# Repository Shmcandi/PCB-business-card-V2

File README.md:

# ESP32-C6 Smart PCB Business Card V2 (96-RGB Matrix + Dual NFC/RFID)

An ultra-slim, monolithic smart electronic business card in the standard ISO/IEC 7810 ID-1 credit card form factor ($85.6 \times 54.0\text{ mm}$), powered by an **Espressif ESP32-C6-MINI-1** microcontroller.

Featuring an ultra-dense **96-LED addressable RGB micro-matrix (WS2812B-2020)** on the front, and a **Dual-Frequency 13.56 MHz NFC + 125 kHz RFID Contactless Engine** on the back with an integrated 4-turn planar spiral antenna etched directly in PCB copper.

Tap against any modern smartphone (iPhone / Android) to instantly deliver your digital portfolio and vCard, or tap against office turnstiles and RFID access readers to unlock doors — with onboard USB-C programming, autonomous Li-Po battery charging, and zero-drain hardware deep sleep.

Everything is engineered for 100% surface-mount assembly with **zero pin headers, zero through-holes, and zero sockets**.

---

## 📸 3D Renders

| Isometric Perspective View | Top View (96-LED Field) | Bottom View (Antenna & Battery Bay) |
| :---: | :---: | :---: |
|  |  |  |

---

## ⚡ Key Specifications & Features

- **Form Factor:** $85.6\text{ mm} \times 54.0\text{ mm} \times 1.6\text{ mm}$ (Standard ID-1 Credit Card Size with $3.18\text{ mm}$ corner radii). Fits standard wallets and card holders.
- **Microcontroller:** **ESP32-C6-MINI-1-N4**
  - High-performance 32-bit RISC-V core (up to 160 MHz) + ultra-low-power RISC-V coprocessor (up to 20 MHz)
  - 2.4 GHz Wi-Fi 6 (802.11ax), Bluetooth 5 (LE), Zigbee 3.0 & Thread (802.15.4 / Matter)
  - Onboard PCB trace antenna with dedicated RF copper clearance keepout
- **Display Matrix:** **96 Addressable RGB Micro-LEDs (WS2812B-2020)**
  - Arranged in a $12 \times 8$ grid ($4.0\text{ mm} \times 4.0\text{ mm}$ pitch) spanning $48.0\text{ mm} \times 32.0\text{ mm}$ across the front
  - Compact $2.0\text{ mm} \times 2.0\text{ mm}$ package with integrated constant-current driver ICs
  - Full 24-bit true color (16.7 million colors) per pixel, driven over a single high-speed GPIO line (`GPIO14`)
  - Serpentine daisy-chain layout with optimized collinear traces for maximum signal integrity
- **Dual-Frequency Contactless Subsystem (NFC + RFID):**
  1. **13.56 MHz High-Frequency NFC (ISO 14443A / NFC Forum Type 2):**
     - Powered by **NXP NTAG I2C Plus (`NT3H2111W0FHK`)** in a TSSOP-8 package
     - Connected to a **4-turn rectangular planar spiral loop antenna** etched directly into the bottom copper layer (`B_Cu`)
     - Resonates at $13.56\text{ MHz}$ with NTAG's $50\text{ pF}$ internal tuning capacitance
     - **Dual Interface:** Operates 100% passively without battery from the smartphone's RF field, and updates dynamically over I2C (`GPIO6` / `GPIO7`) from the ESP32-C6
     - **Field Detect Interrupt (`GPIO18`):** Wakes the ESP32 from deep sleep or triggers LED celebration animations when a smartphone is tapped
  2. **125 kHz Low-Frequency RFID (Building & Door Access):**
     - Powered by **Atmel/Microchip T5577 (`ATA5577C`)** transponder IC in SOIC-8
     - Emulates 125 kHz proximity cards (EM4100 / EM4200 40-bit IDs, HID ProxCard II, Indala) for office doors and turnstiles
     - Dual antenna interface: SMD 1812 transponder inductor (`L1`) + dedicated solder pads (`J3`) for thin wound enamel wire coils
     - **Active Modulation:** Features an onboard **BSS138 N-channel MOSFET (`Q2`)** driven by `GPIO1` (`RFID_MOD`) enabling active software-defined Manchester load modulation
- **Hardware Deep-Sleep Power Gate (Zero Standby Drain):**
  - Standard WS2812B LEDs consume $\sim 1\text{ mA}$ of static quiescent current per pixel even when turned black ($96\text{ LEDs} \approx 96\text{ mA}$ quiescent draw)
  - Incorporates an onboard **Diodes Inc DMG2305UX P-Channel MOSFET** load switch driven by `GPIO5` (`LED_EN`)
  - Physically disconnects the $V_{LED}$ power rail during ESP32 deep sleep, reducing standby current to microamps and enabling months of battery life
- **USB-C Interface:**
  - GCT USB4105 16-pin USB Type-C receptacle with $5.1\text{ k}\Omega$ CC pull-down resistors (compliant with USB-C PD / fast chargers)
  - Native USB-Serial/JTAG directly connected to ESP32-C6 `GPIO12` (D-) and `GPIO13` (D+) for instant flashing and serial logging without external UART bridges
- **Power & Li-Po Battery Charging:**
  - Autonomous Li-Po charger: Microchip **MCP73831T-2ACI/OT** ($300\text{ mA}$ charge rate) with red charging status LED (`CHG`)
  - High-efficiency LDO regulator: Diodes Inc **AP2112K-3.3** ($600\text{ mA}$ peak current, $55\,\mu\text{A}$ quiescent current, low dropout voltage)
  - Battery connector: SMD horizontal JST-PH 2-pin connector (`J2`) + dedicated rear $30 \times 25\text{ mm}$ silkscreen area for mounting an ultra-slim $3.7\text{V}$ Li-Po pouch cell (`302030` / `402030`, $150\text{–}250\text{ mAh}$)
- **Interactive Tactile Controls:**
  - `EN` (Reset) tactile switch (`SW1`) with RC debounce filter
  - `BOOT` (`GPIO9`) tactile switch (`SW2`) for firmware download / user interaction
  - `USER` (`GPIO4`) tactile switch (`SW3`) for mode cycling / games / menu navigation

---

## 📌 ESP32-C6 Pinout & Signal Mapping

| Signal | ESP32-C6 Pin | GPIO / Function | Electrical Type | Description |
| :--- | :---: | :---: | :---: | :--- |
| **LED_DIN** | Pin 19 | GPIO14 | Digital Output | Matrix Serial Data Input (800 kHz NZR stream) |
| **LED_EN** | Pin 10 | GPIO5 | Digital Output | LED Power Gate (Active-LOW: `LOW` = ON, `HIGH` = OFF) |
| **I2C_SDA** | Pin 12 | GPIO6 | I2C Open-Drain | NTAG I2C Plus Serial Data Line (4.7k pull-up to 3.3V) |
| **I2C_SCL** | Pin 13 | GPIO7 | I2C Open-Drain | NTAG I2C Plus Serial Clock Line (4.7k pull-up to 3.3V) |
| **NFC_FD** | Pin 24 | GPIO18 | Digital Input | NTAG Field Detect Interrupt (Active-LOW with 10k pull-up) |
| **RFID_MOD**| Pin 6 | GPIO1 | Digital Output | 125 kHz Active Load Modulation Gate via Q2 BSS138 |
| **USER_SW** | Pin 9 | GPIO4 | Digital Input | Tactile Pushbutton (Active-LOW with internal pull-up) |
| **BOOT_SW** | Pin 23 | GPIO9 | Digital Input | Boot Mode / User Button 2 (Active-LOW) |
| **RESET_SW**| Pin 8 | CHIP_EN | Reset / Enable | Active-LOW Hardware Reset with 10k pull-up + 100nF filter |
| **USB D-** | Pin 17 | GPIO12 | Differential D- | Native ESP32 USB-Serial/JTAG Data Minus |
| **USB D+** | Pin 18 | GPIO13 | Differential D+ | Native ESP32 USB-Serial/JTAG Data Plus |
| **CHG_STAT**| — | — | Open-Drain | MCP73831 Charge Indicator to Red LED `D1` |

---

## 🧮 Matrix Geometry & Serpentine Mapping

The 96 LEDs are placed in an alternating serpentine pattern to minimize trace length and eliminate cross-routing:

```
Row 0 (y=0):  LED  0  <--  LED  1  <-- ... <--  LED 11  (Right-to-Left, 0° rotation)
               |
Row 1 (y=1):  LED 12  -->  LED 13  --> ... -->  LED 23  (Left-to-Right, 180° rotation)
                                                 |
Row 2 (y=2):  LED 24  <--  LED 25  <-- ... <--  LED 35  (Right-to-Left, 0° rotation)
               |
Row 3 (y=3):  ... (repeats for 8 rows, ending at LED 95)
```

### Coordinate Conversion Function (FastLED / NeoPixel)

```cpp
// Map (x, y) coordinates where x is [0..11] and y is [0..7]
uint16_t XY(uint8_t x, uint8_t y) {
    if (x >= 12 || y >= 8) return 0;
    if (y & 0x01) {
        // Odd rows: Left to Right
        return (y * 12) + x;
    } else {
        // Even rows: Right to Left
        return (y * 12) + (11 - x);
    }
}
```

---

## 📦 Hardware & Manufacturing Files

The board is 100% routed and verified with KiCad 10 DRC (0 unconnected items, 0 clearance errors), ready for turnkey assembly at JLCPCB / PCBWay:

- **KiCad PCB:** [`card_v2.kicad_pcb`](card_v2.kicad_pcb)
- **KiCad Project:** [`card_v2.kicad_pro`](card_v2.kicad_pro)
- **Order-Ready Gerbers Archive:** [`pcb_business_card_v2_gerbers.zip`](pcb_business_card_v2_gerbers.zip)
- **Bill of Materials (BOM):** [`fab_v2/BOM.csv`](fab_v2/BOM.csv)
- **Pick-and-Place Centroids (CPL):** [`fab_v2/CPL.csv`](fab_v2/CPL.csv)
- **Custom Footprints:** [`custom.pretty/`](custom.pretty/)

### Recommended Fabrication Settings:
| Parameter | Recommended Value |
| :--- | :--- |
| **Layers** | 2 Layers |
| **PCB Thickness** | 1.6 mm (standard) or 1.0 mm (ultra-slim wallet profile) |
| **Solder Mask** | Matte Black (best contrast for RGB LEDs) |
| **Silkscreen** | White |
| **Surface Finish** | ENIG (Electroless Nickel Immersion Gold) |
| **Copper Weight** | 1 oz Cu |

---

## 📜 License & Author

Designed and engineered by **Shmcandi**. Released under the **MIT License**.

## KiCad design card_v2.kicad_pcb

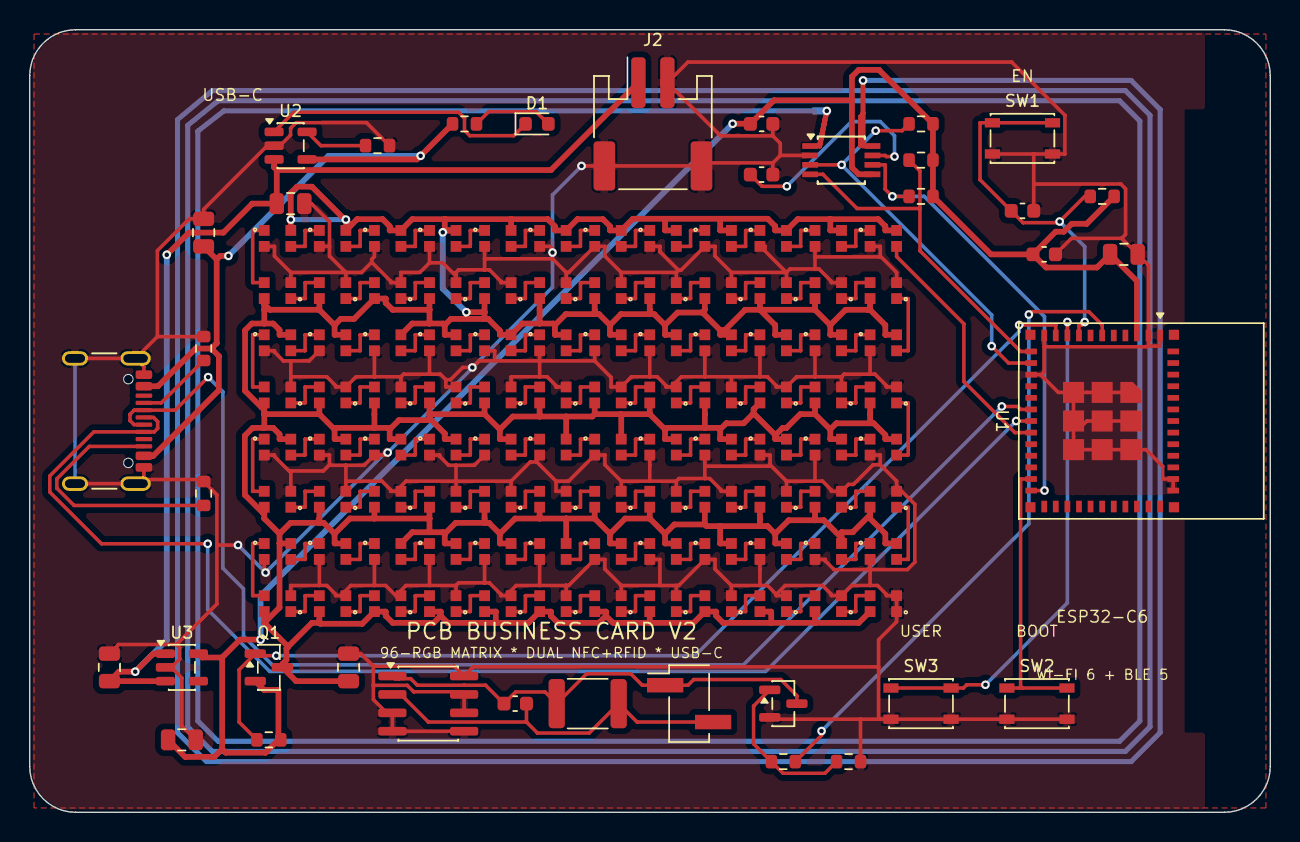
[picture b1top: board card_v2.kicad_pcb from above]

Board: 2 copper layers, 85.6 x 54.0 mm, 134 parts (1 on the bottom side), 122 nets.

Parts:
C1, C2: 4.7uF; C_0805_2012Metric
C3, C4, C6, C8: 10uF; C_0805_2012Metric
C5, C9, C10: 100nF; C_0603_1608Metric
C7: 1uF; C_0603_1608Metric
C12: 470pF; C_0603_1608Metric
D1: CHG; LED_0603_1608Metric
J1: USB-C (USB4105); USB_C_Receptacle_GCT_USB4105-xx-A_16P_TopMnt_Horizontal
J2: BATT JST-PH; JST_PH_S2B-PH-SM4-TB_1x02-1MP_P2.00mm_Horizontal
J3: 125k Wire Pads; PinHeader_1x02_P2.54mm_Vertical_SMD_Pin1Left
L1: 125kHz Coil; L_1812_4532Metric
LED1, LED2, LED3, LED4, LED5, LED6, LED7, LED8, LED9, LED10, LED11, LED12, LED13, LED14, LED15, LED16, LED17, LED18, LED19, LED20, LED21, LED22, LED23, LED24, LED25, LED26, LED27, LED28, LED29, LED30, LED31, LED32, LED33, LED34, LED35, LED36, LED37, LED38, LED39, LED40, LED41, LED42, LED43, LED44, LED45, LED46, LED47, LED48, LED49, LED50, LED51, LED52, LED53, LED54, LED55, LED56, LED57, LED58, LED59, LED60, LED61, LED62, LED63, LED64, LED65, LED66, LED67, LED68, LED69, LED70, LED71, LED72, LED73, LED74, LED75, LED76, LED77, LED78, LED79, LED80, LED81, LED82, LED83, LED84, LED85, LED86, LED87, LED88, LED89, LED90, LED91, LED92, LED93, LED94, LED95, LED96: WS2812B-2020; LED_WS2812B-2020
NT1: NetTie-2; NetTie-2_SMD_Pad0.5mm
Q1: DMG2305UX; SOT-23
Q2: BSS138; SOT-23
R1, R2: 5.1k; R_0603_1608Metric
R3: 3.3k; R_0603_1608Metric
R4, R10: 10k; R_0603_1608Metric
R6, R11: 1k; R_0603_1608Metric
R7, R12: 100k; R_0603_1608Metric
R8, R9: 4.7k; R_0603_1608Metric
SW1: EN; SW_SPST_PTS810
SW2: BOOT; SW_SPST_PTS810
SW3: USER; SW_SPST_PTS810
U1: ESP32-C6-MINI-1-N4; ESP32-C6-MINI-1
U2: MCP73831T-2ACI/OT; SOT-23-5
U3: AP2112K-3.3; SOT-23-5
U4: NT3H2111W0FHK; TSSOP-8_3x3mm_P0.65mm
U5: ATA5577C; SOIC-8_3.9x4.9mm_P1.27mm

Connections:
3V3: C4.1, C5.1, C6.1, C9.1, Q1.2, R4.2, R7.2, R8.2, R9.2, R10.2, U1.3, U3.5, U4.5
BOOT: SW2.1, U1.23
BTN: SW3.1, U1.9
CC1: J1.A5, R1.1
CC2: J1.B5, R2.1
D_SIG_0: LED1.3, U1.19
D_SIG_1: LED1.1, LED2.3
D_SIG_2: LED2.1, LED3.3
D_SIG_3: LED3.1, LED4.3
D_SIG_4: LED4.1, LED5.3
D_SIG_5: LED5.1, LED6.3
D_SIG_6: LED6.1, LED7.3
D_SIG_7: LED7.1, LED8.3
D_SIG_8: LED8.1, LED9.3
D_SIG_9: LED9.1, LED10.3
D_SIG_10: LED10.1, LED11.3
D_SIG_11: LED11.1, LED12.3
D_SIG_12: LED12.1, LED13.3
D_SIG_13: LED13.1, LED14.3
D_SIG_14: LED14.1, LED15.3
D_SIG_15: LED15.1, LED16.3
D_SIG_16: LED16.1, LED17.3
D_SIG_17: LED17.1, LED18.3
D_SIG_18: LED18.1, LED19.3
D_SIG_19: LED19.1, LED20.3
D_SIG_20: LED20.1, LED21.3
D_SIG_21: LED21.1, LED22.3
D_SIG_22: LED22.1, LED23.3
D_SIG_23: LED23.1, LED24.3
D_SIG_24: LED24.1, LED25.3
D_SIG_25: LED25.1, LED26.3
D_SIG_26: LED26.1, LED27.3
D_SIG_27: LED27.1, LED28.3
D_SIG_28: LED28.1, LED29.3
D_SIG_29: LED29.1, LED30.3
D_SIG_30: LED30.1, LED31.3
D_SIG_31: LED31.1, LED32.3
D_SIG_32: LED32.1, LED33.3
D_SIG_33: LED33.1, LED34.3
D_SIG_34: LED34.1, LED35.3
D_SIG_35: LED35.1, LED36.3
D_SIG_36: LED36.1, LED37.3
D_SIG_37: LED37.1, LED38.3
D_SIG_38: LED38.1, LED39.3
D_SIG_39: LED39.1, LED40.3
D_SIG_40: LED40.1, LED41.3
D_SIG_41: LED41.1, LED42.3
D_SIG_42: LED42.1, LED43.3
D_SIG_43: LED43.1, LED44.3
D_SIG_44: LED44.1, LED45.3
D_SIG_45: LED45.1, LED46.3
D_SIG_46: LED46.1, LED47.3
D_SIG_47: LED47.1, LED48.3
D_SIG_48: LED48.1, LED49.3
D_SIG_49: LED49.1, LED50.3
D_SIG_50: LED50.1, LED51.3
D_SIG_51: LED51.1, LED52.3
D_SIG_52: LED52.1, LED53.3
D_SIG_53: LED53.1, LED54.3
D_SIG_54: LED54.1, LED55.3
D_SIG_55: LED55.1, LED56.3
D_SIG_56: LED56.1, LED57.3
D_SIG_57: LED57.1, LED58.3
D_SIG_58: LED58.1, LED59.3
D_SIG_59: LED59.1, LED60.3
D_SIG_60: LED60.1, LED61.3
D_SIG_61: LED61.1, LED62.3
D_SIG_62: LED62.1, LED63.3
D_SIG_63: LED63.1, LED64.3
D_SIG_64: LED64.1, LED65.3
D_SIG_65: LED65.1, LED66.3
D_SIG_66: LED66.1, LED67.3
D_SIG_67: LED67.1, LED68.3
D_SIG_68: LED68.1, LED69.3
D_SIG_69: LED69.1, LED70.3
D_SIG_70: LED70.1, LED71.3
D_SIG_71: LED71.1, LED72.3
D_SIG_72: LED72.1, LED73.3
D_SIG_73: LED73.1, LED74.3
D_SIG_74: LED74.1, LED75.3
D_SIG_75: LED75.1, LED76.3
D_SIG_76: LED76.1, LED77.3
D_SIG_77: LED77.1, LED78.3
D_SIG_78: LED78.1, LED79.3
D_SIG_79: LED79.1, LED80.3
D_SIG_80: LED80.1, LED81.3
D_SIG_81: LED81.1, LED82.3
D_SIG_82: LED82.1, LED83.3
D_SIG_83: LED83.1, LED84.3
D_SIG_84: LED84.1, LED85.3
D_SIG_85: LED85.1, LED86.3
D_SIG_86: LED86.1, LED87.3
D_SIG_87: LED87.1, LED88.3
D_SIG_88: LED88.1, LED89.3
D_SIG_89: LED89.1, LED90.3
D_SIG_90: LED90.1, LED91.3
D_SIG_91: LED91.1, LED92.3
D_SIG_92: LED92.1, LED93.3
D_SIG_93: LED93.1, LED94.3
D_SIG_94: LED94.1, LED95.3
D_SIG_95: LED95.1, LED96.3
EN: C7.1, R4.1, SW1.1, U1.8
GND: C1.2, C2.2, C3.2, C4.2, C5.2, C6.2, C7.2, C8.2, C9.2, C10.2, J1.A1, J1.A12, J1.B1, J1.B12, J1.SH, J2.2, J2.MP, LED1.2, LED2.2, LED3.2, LED4.2, LED5.2, LED6.2, LED7.2, LED8.2, LED9.2, LED10.2, LED11.2, LED12.2, LED13.2, LED14.2, LED15.2, LED16.2, LED17.2, LED18.2, LED19.2, LED20.2, LED21.2, LED22.2, LED23.2, LED24.2, LED25.2, LED26.2, LED27.2, LED28.2, LED29.2, LED30.2, LED31.2, LED32.2, LED33.2, LED34.2, LED35.2, LED36.2, LED37.2, LED38.2, LED39.2, LED40.2, LED41.2, LED42.2, LED43.2, LED44.2, LED45.2, LED46.2, LED47.2, LED48.2, LED49.2, LED50.2, LED51.2, LED52.2, LED53.2, LED54.2, LED55.2, LED56.2, LED57.2, LED58.2, LED59.2, LED60.2, LED61.2, LED62.2, LED63.2, LED64.2, LED65.2, LED66.2, LED67.2, LED68.2, LED69.2, LED70.2, LED71.2, LED72.2, LED73.2, LED74.2, LED75.2, LED76.2, LED77.2, LED78.2, LED79.2, LED80.2, LED81.2, LED82.2, LED83.2, LED84.2, LED85.2, LED86.2, LED87.2, LED88.2, LED89.2, LED90.2, LED91.2, LED92.2, LED93.2, LED94.2, LED95.2, LED96.1, LED96.2, Q2.2, R1.2, R2.2, R3.2, R12.2, SW1.2, SW2.2, SW3.2, U1.1, U1.2, U1.11, U1.14, U1.36, U1.37, U1.49, U2.2, U3.2, U4.2, U5.3, U5.4, U5.5, U5.6, U5.7, U5.8
I2C_SCL: R8.1, U1.13, U4.3
I2C_SDA: R9.1, U1.12, U4.4
LEDA: D1.2, R6.2
LED_EN: Q1.1, R7.1, U1.10
NFC_ANT_A: NT1.1, U4.1
NFC_ANT_B: NT1.2, U4.8
NFC_FD: R10.1, U1.24, U4.6
PROG: R3.1, U2.5
RFID_COIL1: C12.1, J3.1, L1.1, Q2.3, U5.1
RFID_COIL2: C12.2, J3.2, L1.2, U5.2
RFID_GATE: Q2.1, R11.1, R12.1
RFID_MOD: R11.2, U1.6
STAT: D1.1, U2.1
USB_DN: J1.A7, J1.B7, U1.17
USB_DP: J1.A6, J1.B6, U1.18
VBAT: C2.1, C3.1, J2.1, U2.3, U3.1, U3.3
VBUS: C1.1, J1.A4, J1.A9, J1.B4, J1.B9, R6.1, U2.4
VLED: C8.1, LED1.4, LED2.4, LED3.4, LED4.4, LED5.4, LED6.4, LED7.4, LED8.4, LED9.4, LED10.4, LED11.4, LED12.4, LED13.4, LED14.4, LED15.4, LED16.4, LED17.4, LED18.4, LED19.4, LED20.4, LED21.4, LED22.4, LED23.4, LED24.4, LED25.4, LED26.4, LED27.4, LED28.4, LED29.4, LED30.4, LED31.4, LED32.4, LED33.4, LED34.4, LED35.4, LED36.4, LED37.4, LED38.4, LED39.4, LED40.4, LED41.4, LED42.4, LED43.4, LED44.4, LED45.4, LED46.4, LED47.4, LED48.4, LED49.4, LED50.4, LED51.4, LED52.4, LED53.4, LED54.4, LED55.4, LED56.4, LED57.4, LED58.4, LED59.4, LED60.4, LED61.4, LED62.4, LED63.4, LED64.4, LED65.4, LED66.4, LED67.4, LED68.4, LED69.4, LED70.4, LED71.4, LED72.4, LED73.4, LED74.4, LED75.4, LED76.4, LED77.4, LED78.4, LED79.4, LED80.4, LED81.4, LED82.4, LED83.4, LED84.4, LED85.4, LED86.4, LED87.4, LED88.4, LED89.4, LED90.4, LED91.4, LED92.4, LED93.4, LED94.4, LED95.4, LED96.4, Q1.3
VOUT_NFC: C10.1, U4.7

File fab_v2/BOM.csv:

Comment/Value,Designator,Footprint,Quantity
100k,"R7, R12",R_0603_1608Metric,2
100nF,"C5, C9, C10",C_0603_1608Metric,3
10k,"R4, R10",R_0603_1608Metric,2
10uF,"C3, C4, C6, C8",C_0805_2012Metric,4
125k Wire Pads,J3,PinHeader_1x02_P2.54mm_Vertical_SMD_Pin1Left,1
125kHz Coil,L1,L_1812_4532Metric,1
1k,"R6, R11",R_0603_1608Metric,2
1uF,C7,C_0603_1608Metric,1
3.3k,R3,R_0603_1608Metric,1
4.7k,"R8, R9",R_0603_1608Metric,2
4.7uF,"C1, C2",C_0805_2012Metric,2
470pF,C12,C_0603_1608Metric,1
5.1k,"R1, R2",R_0603_1608Metric,2
AP2112K-3.3,U3,SOT-23-5,1
ATA5577C,U5,SOIC-8_3.9x4.9mm_P1.27mm,1
BATT JST-PH,J2,JST_PH_S2B-PH-SM4-TB_1x02-1MP_P2.00mm_Horizontal,1
BOOT,SW2,SW_SPST_PTS810,1
BSS138,Q2,SOT-23,1
CHG,D1,LED_0603_1608Metric,1
DMG2305UX,Q1,SOT-23,1
EN,SW1,SW_SPST_PTS810,1
ESP32-C6-MINI-1-N4,U1,ESP32-C6-MINI-1,1
MCP73831T-2ACI/OT,U2,SOT-23-5,1
NT3H2111W0FHK,U4,TSSOP-8_3x3mm_P0.65mm,1
NetTie-2,NT1,NetTie-2_SMD_Pad0.5mm,1
USB-C (USB4105),J1,USB_C_Receptacle_GCT_USB4105-xx-A_16P_TopMnt_Horizontal,1
USER,SW3,SW_SPST_PTS810,1
WS2812B-2020,"LED59, LED55, LED26, LED87, LED67, LED21, LED79, LED37, LED25, LED44, LED96, LED93, LED6, LED15, LED63, LED66, LED94, LED13, LED18, LED60, LED12, LED46, LED78, LED86, LED28, LED75, LED89, LED19, LED29, LED43, LED56, LED20, LED34, LED52, LED64, LED69, LED82, LED83, LED33, LED80, LED38, LED42, LED9, LED48, LED40, LED51, LED8, LED50, LED74, LED32, LED22, LED88, LED2, LED17, LED1, LED4, LED11, LED58, LED3, LED7, LED65, LED77, LED85, LED39, LED71, LED76, LED53, LED61, LED45, LED14, LED23, LED16, LED47, LED24, LED5, LED10, LED49, LED84, LED90, LED95, LED41, LED62, LED68, LED91, LED27, LED73, LED35, LED72, LED54, LED31, LED92, LED57, LED70, LED81, LED36, LED30",LED_WS2812B-2020,96

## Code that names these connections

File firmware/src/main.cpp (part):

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#define LED_PWR_PIN      5    // DMG2305UX P-MOSFET Gate (LOW = ON, HIGH = OFF)
#define BTN_USER_PIN     4    // USER tactile switch (active LOW)
#define BTN_BOOT_PIN     9    // BOOT tactile switch (active LOW)
#define I2C_SDA_PIN      6    // NTAG I2C Plus SDA
#define I2C_SCL_PIN      7    // NTAG I2C Plus SCL
#define NFC_FD_PIN       18   // NTAG I2C Field Detect Interrupt (active LOW)
#define RFID_MOD_PIN     1    // 125 kHz Active RFID Load Modulator (Q2 BSS138)

// NXP NTAG I2C Plus Address
#define NTAG_I2C_ADDR    0x55
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 */
void disableLEDSupply() {
    FastLED.clear(true);
    digitalWrite(LED_PWR_PIN, HIGH); // Disconnect VLED rail
}

/**
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    disableLEDSupply();
    // Wake up when either USER button is pressed OR a phone taps the NFC antenna!
    esp_deep_sleep_enable_gpio_wakeup(1ULL << BTN_USER_PIN, ESP_GPIO_WAKEUP_GPIO_LOW);
    esp_deep_sleep_enable_gpio_wakeup(1ULL << NFC_FD_PIN, ESP_GPIO_WAKEUP_GPIO_LOW);
    esp_deep_sleep_start();
}

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    // Standard EM4100 frame: 9 header bits (1s) + 10 nibbles with row parity + 4 column parity + 1 stop bit
    // Modulate on GPIO1 at 2 kBaud (64 clock cycles per bit at 125 kHz -> ~512us per bit period)
    const uint16_t halfBitUs = 256;
    pinMode(RFID_MOD_PIN, OUTPUT);

    auto sendBit = [&](bool bit) {
        // Manchester encoding: 0 = Low-to-High, 1 = High-to-Low
        digitalWrite(RFID_MOD_PIN, bit ? HIGH : LOW);
        delayMicroseconds(halfBitUs);
        digitalWrite(RFID_MOD_PIN, bit ? LOW : HIGH);
        delayMicroseconds(halfBitUs);
    };

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
    // Stop bit (always 0)
    sendBit(0);
    digitalWrite(RFID_MOD_PIN, LOW);
}

/**
 * @brief Initialize NXP NTAG I2C Plus chip over I2C.
 */
void initNTAG() {
    Wire.begin(I2C_SDA_PIN, I2C_SCL_PIN, 400000);
    Wire.beginTransmission(NTAG_I2C_ADDR);
    if (Wire.endTransmission() == 0) {
        Serial.println("[NFC] NXP NTAG I2C Plus online (Address 0x55)");
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    // 2. Configure tactile inputs & interrupts
    pinMode(BTN_USER_PIN, INPUT_PULLUP);
    pinMode(BTN_BOOT_PIN, INPUT_PULLUP);
    pinMode(NFC_FD_PIN, INPUT_PULLUP);
    attachInterrupt(digitalPinToInterrupt(NFC_FD_PIN), onNfcFieldDetect, FALLING);

    // 3. Initialize I2C and NTAG dynamic tag
    initNTAG();
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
